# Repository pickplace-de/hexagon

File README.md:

# HEXAGON
HEXAGON is an open hardwrae development board built around 480 MHz Renesas MCU (Arm® Cortex®-M85 core with HeliumTM).<br/>
The board was designed as there was nothing similar meeting our demands at the moment.<br/>
Along with Cortex®-M85 in BGA package the hardware design also includes:<br/>
✔ 8 MB SDRAM<br/>
✔ 32 MB QSPI<br/>
✔ Stereo Audio Codec (for voice recognition applications development) with 3.5mm jack connector for headphones and microphone<br/>
✔ USB interface with USB-C connector (MCU USB and/or power)<br/>
✔ Ethernet interface with RJ45<br/>
✔ CAN interface with D-SUB connector<br/>
✔ RS485 interface with D-SUB connector<br/>
✔ Flexible power supply (from 5 to 30VDC) with barrel jack connector and an option to power the board from USB<br/>
✔ Reset button and power supply LEDs<br/>
✔ 2 user buttons and 3 user LEDs<br/>

## Hardware
The board design contains 8 layers including 4 signal layers, 3 ground planes and 1 power plane.<br/>
Some components (MCU, QSPI) are in BGA packages and may be hard to assembly manually.<br/>

## License
This project is licensed under **CERN-OHL-W-2.0**, which allows modification and commercial use with attribution.<br/>
See the  for full details.

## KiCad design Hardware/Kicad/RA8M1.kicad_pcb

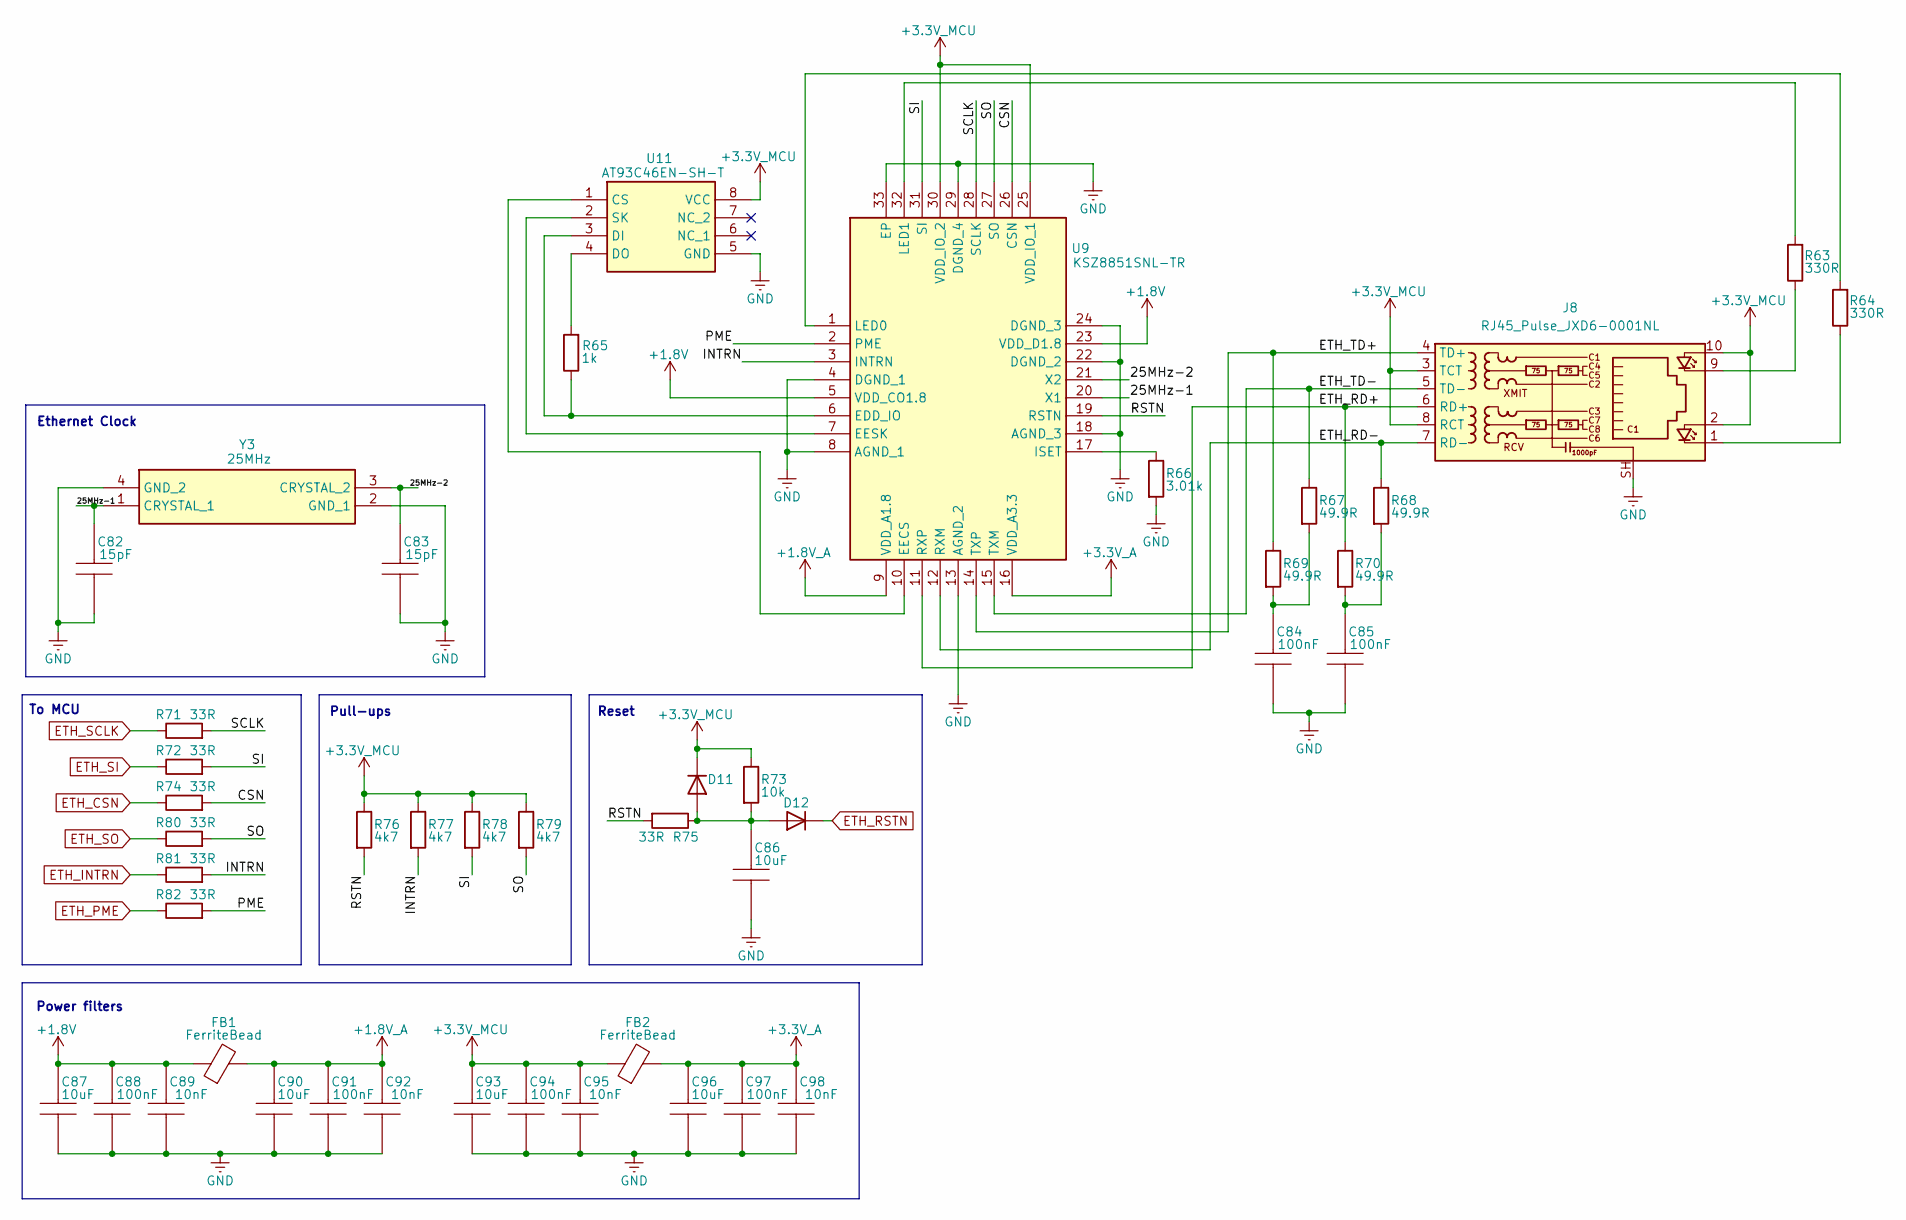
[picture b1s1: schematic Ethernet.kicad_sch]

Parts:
C82, C83: 15pF; C_0402_1005Metric; MPN 885012005008
C84, C85, C88, C91, C94, C97: 100nF; C_0402_1005Metric; MPN 885012205092
C86, C87, C90, C93, C96: 10uF; C_0402_1005Metric; MPN 885012105020
C89, C92, C95, C98: 10nF; C_0402_1005Metric; MPN 885012205031
D11, D12: 1N4148W; D_SOD-123; MPN 1N4148W-7-F
FB1, FB2: FerriteBead; L_0805_2012Metric; MPN 742792040
J8: RJ45_Pulse_JXD6-0001NL; RJ45_Pulse_JXD6-0001NL_Horizontal; MPN JXD6-0001NL
R63, R64: 330R; R_0402_1005Metric; MPN 560112110231
R65: 1k; R_0402_1005Metric; MPN 560112110012
R66: 3.01k; R_0402_1005Metric; MPN CR0402-FX-3011GLF
R67, R68, R69, R70: 49.9R; R_0402_1005Metric; MPN 560112110002
R71, R72, R74, R75, R80, R81, R82: 33R; R_0402_1005Metric; MPN 560112110004
R73: 10k; R_0402_1005Metric; MPN 560112110020
R76, R77, R78, R79: 4k7; R_0402_1005Metric; MPN 560112110245
U9: KSZ8851SNL-TR; QFN50P500X500X100-33N-D; Mouser Part Number 998-KSZ8851SNLTR
U11: AT93C46EN-SH-T; SOIC127P600X175-8N; Mouser Part Number 556-A93C46ENSHT
Y3: 25MHz; 830108208209; Mouser Part Number 830107871909

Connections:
+1.8V: C87.2, C88.2, C89.2, FB1.1, U9.5 (VDD_CO1.8), U9.23 (VDD_D1.8); also elsewhere on the board
+1.8V_A: C90.2, C91.2, C92.2, FB1.2, U9.9 (VDD_A1.8)
+3.3V_A: C96.2, C97.2, C98.2, FB2.2, U9.16 (VDD_A3.3)
+3.3V_MCU: C93.2, C94.2, C95.2, D11.1 (K), FB2.1, J8.2, J8.3 (TCT), J8.8 (RCT), J8.10, R73.1, R76.1, R77.1, R78.1, R79.1, U9.25 (VDD_IO_1), U9.30 (VDD_IO_2), U11.8 (VCC); also elsewhere on the board
/ETHERNET/25MHz-1: C82.2, U9.20 (X1), Y3.1 (CRYSTAL_1)
/ETHERNET/25MHz-2: C83.2, U9.21 (X2), Y3.3 (CRYSTAL_2)
/ETHERNET/CSN: R74.2, U9.26 (CSN)
/ETHERNET/ETH_RD+: J8.6 (RD+), R70.1, U9.11 (RXP)
/ETHERNET/ETH_RD-: J8.7 (RD-), R68.1, U9.12 (RXM)
/ETHERNET/ETH_TD+: J8.4 (TD+), R69.1, U9.14 (TXP)
/ETHERNET/ETH_TD-: J8.5 (TD-), R67.1, U9.15 (TXM)
/ETHERNET/INTRN: R77.2, R81.2, U9.3 (INTRN)
/ETHERNET/PME: R82.2, U9.2 (PME)
/ETHERNET/RSTN: R75.2, R76.2, U9.19 (RSTN)
/ETHERNET/SCLK: R71.2, U9.28 (SCLK)
/ETHERNET/SI: R72.2, R78.2, U9.31 (SI)
/ETHERNET/SO: R79.2, R80.2, U9.27 (SO)
ETH_CSN: R74.1; also elsewhere on the board
ETH_INTRN: R81.1; also elsewhere on the board
ETH_PME: R82.1; also elsewhere on the board
ETH_RSTN: D12.1 (K); also elsewhere on the board
ETH_SCLK: R71.1; also elsewhere on the board
ETH_SI: R72.1; also elsewhere on the board
ETH_SO: R80.1; also elsewhere on the board
GND: C82.1, C83.1, C84.1, C85.1, C86.1, C87.1, C88.1, C89.1, C90.1, C91.1, C92.1, C93.1, C94.1, C95.1, C96.1, C97.1, C98.1, J8.SH, R66.2, U9.4 (DGND_1), U9.8 (AGND_1), U9.13 (AGND_2), U9.18 (AGND_3), U9.22 (DGND_2), U9.24 (DGND_3), U9.29 (DGND_4), U9.33 (EP), U11.5 (GND), Y3.2 (GND_1), Y3.4 (GND_2); also elsewhere on the board
unnamed: C84.2, R67.2, R69.2
unnamed: C85.2, R68.2, R70.2
unnamed: C86.2, D11.2 (A), D12.2 (A), R73.2, R75.1
unnamed: J8.1, R64.1
unnamed: J8.9, R63.1
unnamed: R66.1, U9.17 (ISET)
unnamed: R64.2, U9.1 (LED0)
unnamed: R63.2, U9.32 (LED1)
unnamed: U9.10 (EECS), U11.1 (CS)
unnamed: R65.1, U9.6 (EDD_IO), U11.3 (DI)
unnamed: R65.2, U11.4 (DO)
unnamed: U9.7 (EESK), U11.2 (SK)

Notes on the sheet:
Power filters
To MCU
Pull-ups
Reset
Ethernet Clock

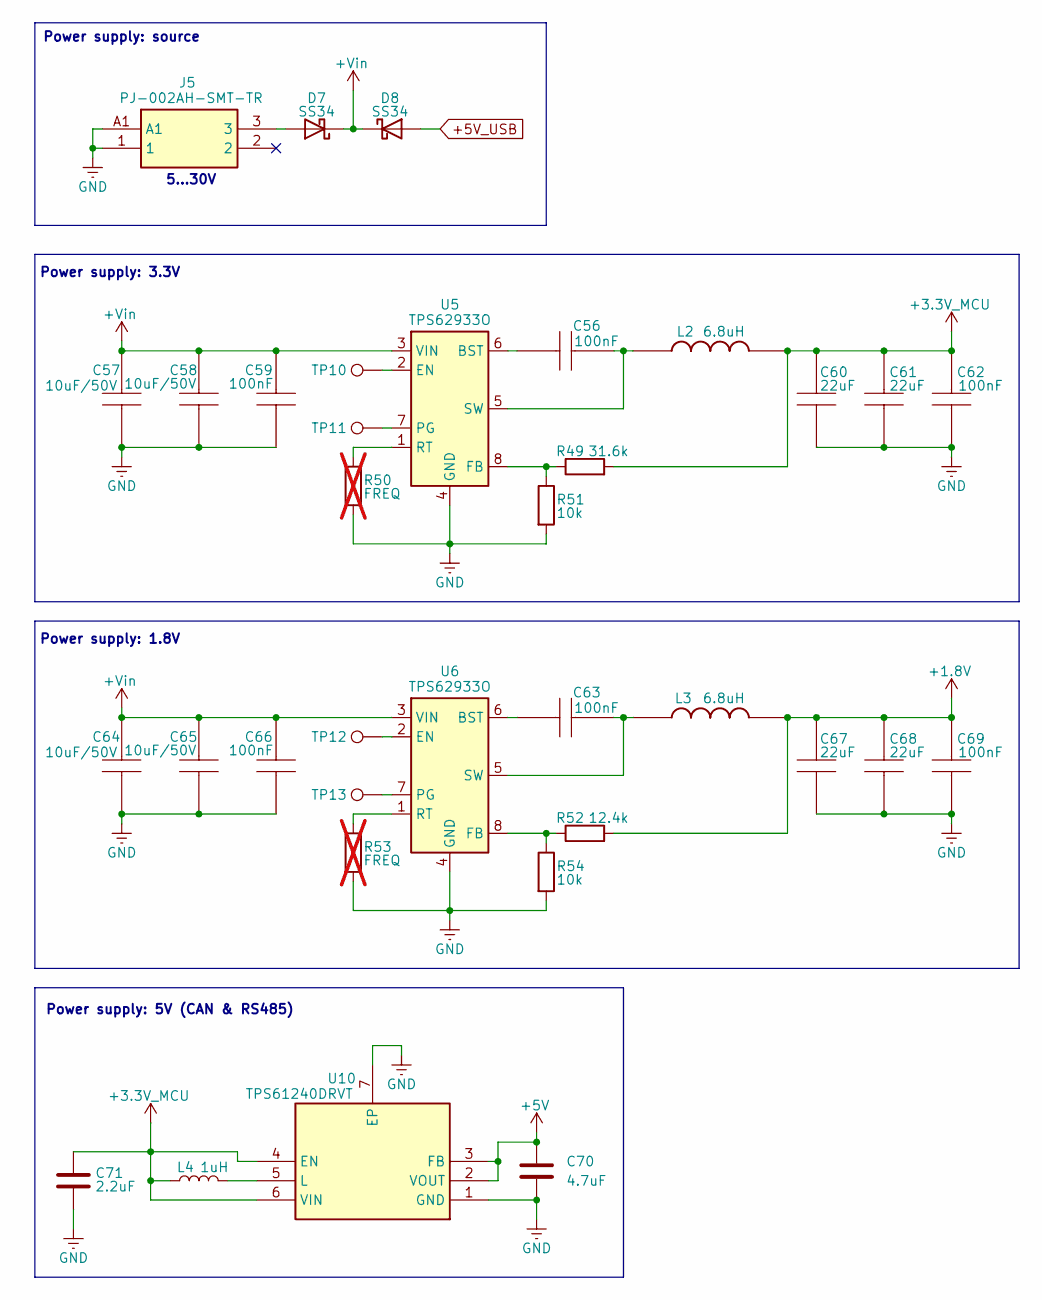
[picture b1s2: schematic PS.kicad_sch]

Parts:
C56, C59, C62, C63, C66, C69: 100nF; C_0402_1005Metric; MPN 885012205092
C57, C58, C64, C65: 10uF/50V; C_0805_2012Metric; MPN C2012X5R1H106K125AC
C60, C61, C67, C68: 22uF; C_0805_2012Metric; MPN 885012107005
C70: 4.7uF; C_0402_1005Metric; MPN 885012105008
C71: 2.2uF; C_0402_1005Metric; MPN 885012105007
D7, D8: SS34; D_SMA
J5: PJ-002AH-SMT-TR; PJ002AHSMTTR; Mouser Part Number 490-PJ-002AH-SMT-TR
L2, L3: 6.8uH; INDPM4141X310N; Mouser Part Number 710-74438357068
L4: 1uH; L_0603_1608Metric; MPN 74479763210A
R49: 31.6k; R_0402_1005Metric; MPN CR0603-FX-3162ELF
R50, R53: FREQ; R_0402_1005Metric; MPN 560112110001; not fitted
R51, R54: 10k; R_0402_1005Metric; MPN 560112110020
R52: 12.4k; R_0402_1005Metric; MPN CR0402-FX-1242GLF
TP10, TP11, TP12, TP13: TestPoint_0.5mm
U5, U6: TPS62933O; SOT-583-8; MPN TPS62933ODRLR
U10: TPS61240DRVT; SON65P200X200X80-7N; Mouser Part Number 595-TPS61240DRVT

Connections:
+1.8V: C67.2, C68.2, C69.2, L3.2, R52.2; also elsewhere on the board
+3.3V_MCU: C60.2, C61.2, C62.2, C71.1, L2.2, L4.1, R49.2, U10.4 (EN), U10.6 (VIN); also elsewhere on the board
+5V: C70.1, U10.2 (VOUT), U10.3 (FB); also elsewhere on the board
+5V_USB: D8.2 (A); also elsewhere on the board
+Vin: C57.2, C58.2, C59.2, C64.2, C65.2, C66.2, D7.1 (K), D8.1 (K), U5.3 (VIN), U6.3 (VIN)
GND: C57.1, C58.1, C59.1, C60.1, C61.1, C62.1, C64.1, C65.1, C66.1, C67.1, C68.1, C69.1, C70.2, C71.2, J5.1, J5.A1, R50.2, R51.2, R53.2, R54.2, U5.4 (GND), U6.4 (GND), U10.1 (GND), U10.7 (EP); also elsewhere on the board
unnamed: D7.2 (A), J5.3
unnamed: C56.2, U5.6 (BST)
unnamed: TP10.1, U5.2 (EN)
unnamed: R49.1, R51.1, U5.8 (FB)
unnamed: TP11.1, U5.7 (PG)
unnamed: R50.1, U5.1 (RT)
unnamed: C56.1, L2.1, U5.5 (SW)
unnamed: C63.2, U6.6 (BST)
unnamed: TP12.1, U6.2 (EN)
unnamed: R52.1, R54.1, U6.8 (FB)
unnamed: TP13.1, U6.7 (PG)
unnamed: R53.1, U6.1 (RT)
unnamed: C63.1, L3.1, U6.5 (SW)
unnamed: L4.2, U10.5 (L)

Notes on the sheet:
Power supply: 5V (CAN & RS485)
Power supply: 3.3V
Power supply: source
Power supply: 1.8V
5...30V

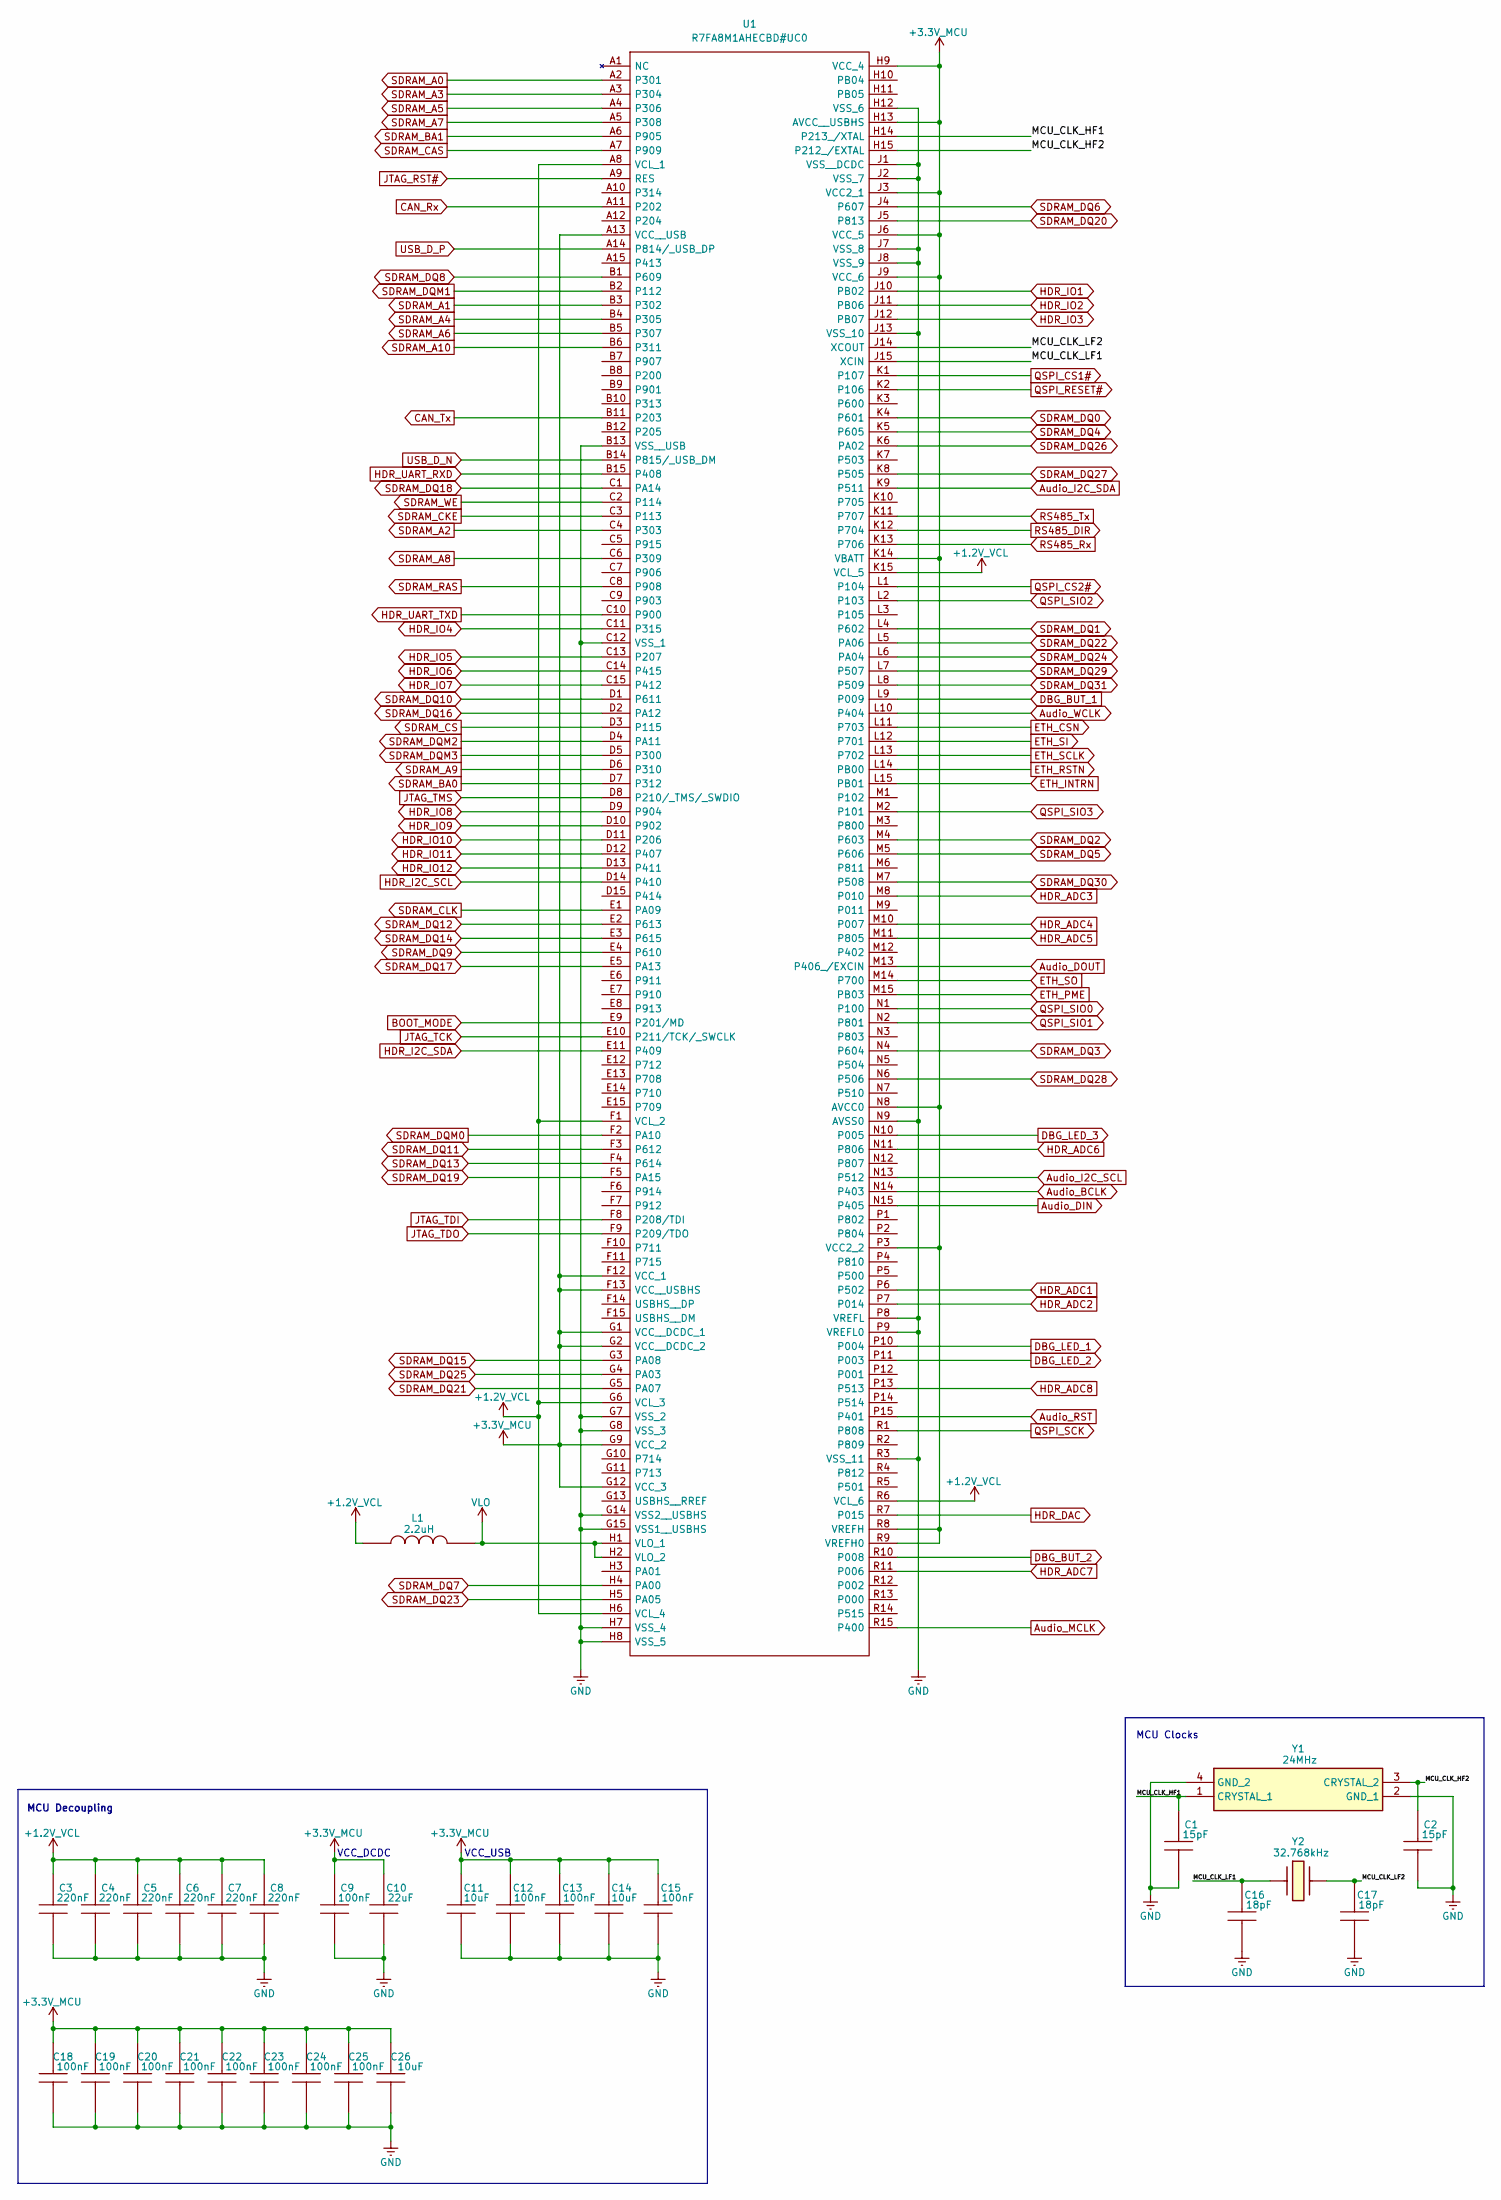
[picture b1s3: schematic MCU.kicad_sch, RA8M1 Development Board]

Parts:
C1, C2: 15pF; C_0402_1005Metric; MPN 885012005008
C3, C4, C5, C6, C7, C8: 220nF; C_0402_1005Metric; MPN 885012105011
C9, C12, C13, C15, C18, C19, C20, C21, C22, C23, C24, C25: 100nF; C_0402_1005Metric; MPN 885012205092
C10: 22uF; C_0805_2012Metric; MPN 885012107005
C11, C14, C26: 10uF; C_0402_1005Metric; MPN 885012105020
C16, C17: 18pF; C_0402_1005Metric; MPN 04023A180CAT2A
L1: 2.2uH; LQM21PHR47NG0D; Mouser Part Number 81-LQM21PN2R2NGCDCD
U1: R7FA8M1AHECBD#UC0; BGA225C80P15X15_1300X1300X147; MPN R7FA8M1AHECBD#UC0
Y1: 24MHz; 830108208209; Mouser Part Number 710-830108208209
Y2: 32.768kHz; 830050789; Mouser Part Number 710-830050789

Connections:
+1.2V_VCL: C3.2, C4.2, C5.2, C6.2, C7.2, C8.2, L1.2, U1.A8 (VCL_1), U1.F1 (VCL_2), U1.G6 (VCL_3), U1.H6 (VCL_4), U1.K15 (VCL_5), U1.R6 (VCL_6)
+3.3V_MCU: C9.2, C10.2, C11.2, C12.2, C13.2, C14.2, C15.2, C18.2, C19.2, C20.2, C21.2, C22.2, C23.2, C24.2, C25.2, C26.2, U1.A13 (VCC__USB), U1.F12 (VCC_1), U1.F13 (VCC__USBHS), U1.G1 (VCC__DCDC_1), U1.G2 (VCC__DCDC_2), U1.G9 (VCC_2), U1.G12 (VCC_3), U1.H9 (VCC_4), U1.H13 (AVCC__USBHS), U1.J3 (VCC2_1), U1.J6 (VCC_5), U1.J9 (VCC_6), U1.K14 (VBATT), U1.N8 (AVCC0), U1.P3 (VCC2_2), U1.R8 (VREFH), U1.R9 (VREFH0); also elsewhere on the board
/MCU/MCU_CLK_HF1: C1.2, U1.H14 (P213_/XTAL), Y1.1 (CRYSTAL_1)
/MCU/MCU_CLK_HF2: C2.2, U1.H15 (P212_/EXTAL), Y1.3 (CRYSTAL_2)
/MCU/MCU_CLK_LF1: C16.2, U1.J15 (XCIN), Y2.1
/MCU/MCU_CLK_LF2: C17.2, U1.J14 (XCOUT), Y2.2
Audio_BCLK: U1.N14 (P403); also elsewhere on the board
Audio_DIN: U1.N15 (P405); also elsewhere on the board
Audio_DOUT: U1.M13 (P406_/EXCIN); also elsewhere on the board
Audio_I2C_SCL: U1.N13 (P512); also elsewhere on the board
Audio_I2C_SDA: U1.K9 (P511); also elsewhere on the board
Audio_MCLK: U1.R15 (P400); also elsewhere on the board
Audio_RST: U1.P15 (P401); also elsewhere on the board
Audio_WCLK: U1.L10 (P404); also elsewhere on the board
BOOT_MODE: U1.E9 (P201/MD); also elsewhere on the board
CAN_Rx: U1.A11 (P202); also elsewhere on the board
CAN_Tx: U1.B11 (P203); also elsewhere on the board
DBG_BUT_1: U1.L9 (P009); also elsewhere on the board
DBG_BUT_2: U1.R10 (P008); also elsewhere on the board
DBG_LED_1: U1.P10 (P004); also elsewhere on the board
DBG_LED_2: U1.P11 (P003); also elsewhere on the board
DBG_LED_3: U1.N10 (P005); also elsewhere on the board
ETH_CSN: U1.L11 (P703); also elsewhere on the board
ETH_INTRN: U1.L15 (PB01); also elsewhere on the board
ETH_PME: U1.M15 (PB03); also elsewhere on the board
ETH_RSTN: U1.L14 (PB00); also elsewhere on the board
ETH_SCLK: U1.L13 (P702); also elsewhere on the board
ETH_SI: U1.L12 (P701); also elsewhere on the board
ETH_SO: U1.M14 (P700); also elsewhere on the board
GND: C1.1, C2.1, C3.1, C4.1, C5.1, C6.1, C7.1, C8.1, C9.1, C10.1, C11.1, C12.1, C13.1, C14.1, C15.1, C16.1, C17.1, C18.1, C19.1, C20.1, C21.1, C22.1, C23.1, C24.1, C25.1, C26.1, U1.B13 (VSS__USB), U1.C12 (VSS_1), U1.G7 (VSS_2), U1.G8 (VSS_3), U1.G14 (VSS2__USBHS), U1.G15 (VSS1__USBHS), U1.H7 (VSS_4), U1.H8 (VSS_5), U1.H12 (VSS_6), U1.J1 (VSS__DCDC), U1.J2 (VSS_7), U1.J7 (VSS_8), U1.J8 (VSS_9), U1.J13 (VSS_10), U1.N9 (AVSS0), U1.P8 (VREFL), U1.P9 (VREFL0), U1.R3 (VSS_11), Y1.2 (GND_1), Y1.4 (GND_2); also elsewhere on the board
HDR_ADC1: U1.P6 (P502); also elsewhere on the board
HDR_ADC2: U1.P7 (P014); also elsewhere on the board
HDR_ADC3: U1.M8 (P010); also elsewhere on the board
HDR_ADC4: U1.M10 (P007); also elsewhere on the board
HDR_ADC5: U1.M11 (P805); also elsewhere on the board
HDR_ADC6: U1.N11 (P806); also elsewhere on the board
HDR_ADC7: U1.R11 (P006); also elsewhere on the board
HDR_ADC8: U1.P13 (P513); also elsewhere on the board
HDR_DAC: U1.R7 (P015); also elsewhere on the board
HDR_I2C_SCL: U1.D14 (P410); also elsewhere on the board
HDR_I2C_SDA: U1.E11 (P409); also elsewhere on the board
HDR_IO1: U1.J10 (PB02); also elsewhere on the board
HDR_IO2: U1.J11 (PB06); also elsewhere on the board
HDR_IO3: U1.J12 (PB07); also elsewhere on the board
HDR_IO4: U1.C11 (P315); also elsewhere on the board
HDR_IO5: U1.C13 (P207); also elsewhere on the board
HDR_IO6: U1.C14 (P415); also elsewhere on the board
HDR_IO7: U1.C15 (P412); also elsewhere on the board
HDR_IO8: U1.D9 (P904); also elsewhere on the board
HDR_IO9: U1.D10 (P902); also elsewhere on the board
HDR_IO10: U1.D11 (P206); also elsewhere on the board
HDR_IO11: U1.D12 (P407); also elsewhere on the board
HDR_IO12: U1.D13 (P411); also elsewhere on the board
HDR_UART_RXD: U1.B15 (P408); also elsewhere on the board
HDR_UART_TXD: U1.C10 (P900); also elsewhere on the board
JTAG_RST#: U1.A9 (RES); also elsewhere on the board
JTAG_TCK: U1.E10 (P211/TCK/_SWCLK); also elsewhere on the board
JTAG_TDI: U1.F8 (P208/TDI); also elsewhere on the board
JTAG_TDO: U1.F9 (P209/TDO); also elsewhere on the board
JTAG_TMS: U1.D8 (P210/_TMS/_SWDIO); also elsewhere on the board
QSPI_CS1#: U1.K1 (P107); also elsewhere on the board
QSPI_CS2#: U1.L1 (P104); also elsewhere on the board
QSPI_RESET#: U1.K2 (P106); also elsewhere on the board
QSPI_SCK: U1.R1 (P808); also elsewhere on the board
QSPI_SIO0: U1.N1 (P100); also elsewhere on the board
QSPI_SIO1: U1.N2 (P801); also elsewhere on the board
QSPI_SIO2: U1.L2 (P103); also elsewhere on the board
QSPI_SIO3: U1.M2 (P101); also elsewhere on the board
RS485_DIR: U1.K12 (P704); also elsewhere on the board
RS485_Rx: U1.K13 (P706); also elsewhere on the board
RS485_Tx: U1.K11 (P707); also elsewhere on the board
SDRAM_A0: U1.A2 (P301); also elsewhere on the board
SDRAM_A1: U1.B3 (P302); also elsewhere on the board
SDRAM_A2: U1.C4 (P303); also elsewhere on the board
SDRAM_A3: U1.A3 (P304); also elsewhere on the board
SDRAM_A4: U1.B4 (P305); also elsewhere on the board
SDRAM_A5: U1.A4 (P306); also elsewhere on the board
SDRAM_A6: U1.B5 (P307); also elsewhere on the board
SDRAM_A7: U1.A5 (P308); also elsewhere on the board
SDRAM_A8: U1.C6 (P309); also elsewhere on the board
SDRAM_A9: U1.D6 (P310); also elsewhere on the board
SDRAM_A10: U1.B6 (P311); also elsewhere on the board
SDRAM_BA0: U1.D7 (P312); also elsewhere on the board
SDRAM_BA1: U1.A6 (P905); also elsewhere on the board
SDRAM_CAS: U1.A7 (P909); also elsewhere on the board
SDRAM_CKE: U1.C3 (P113); also elsewhere on the board
SDRAM_CLK: U1.E1 (PA09); also elsewhere on the board
SDRAM_CS: U1.D3 (P115); also elsewhere on the board
SDRAM_DQ0: U1.K4 (P601); also elsewhere on the board
SDRAM_DQ1: U1.L4 (P602); also elsewhere on the board
SDRAM_DQ2: U1.M4 (P603); also elsewhere on the board
SDRAM_DQ3: U1.N4 (P604); also elsewhere on the board
SDRAM_DQ4: U1.K5 (P605); also elsewhere on the board
SDRAM_DQ5: U1.M5 (P606); also elsewhere on the board
SDRAM_DQ6: U1.J4 (P607); also elsewhere on the board
SDRAM_DQ7: U1.H4 (PA00); also elsewhere on the board
SDRAM_DQ8: U1.B1 (P609); also elsewhere on the board
SDRAM_DQ9: U1.E4 (P610); also elsewhere on the board
SDRAM_DQ10: U1.D1 (P611); also elsewhere on the board
SDRAM_DQ11: U1.F3 (P612); also elsewhere on the board
SDRAM_DQ12: U1.E2 (P613); also elsewhere on the board
SDRAM_DQ13: U1.F4 (P614); also elsewhere on the board
SDRAM_DQ14: U1.E3 (P615); also elsewhere on the board
SDRAM_DQ15: U1.G3 (PA08); also elsewhere on the board
SDRAM_DQ16: U1.D2 (PA12); also elsewhere on the board
SDRAM_DQ17: U1.E5 (PA13); also elsewhere on the board
SDRAM_DQ18: U1.C1 (PA14); also elsewhere on the board
SDRAM_DQ19: U1.F5 (PA15); also elsewhere on the board
SDRAM_DQ20: U1.J5 (P813); also elsewhere on the board
SDRAM_DQ21: U1.G5 (PA07); also elsewhere on the board
SDRAM_DQ22: U1.L5 (PA06); also elsewhere on the board
SDRAM_DQ23: U1.H5 (PA05); also elsewhere on the board
SDRAM_DQ24: U1.L6 (PA04); also elsewhere on the board
SDRAM_DQ25: U1.G4 (PA03); also elsewhere on the board
SDRAM_DQ26: U1.K6 (PA02); also elsewhere on the board
SDRAM_DQ27: U1.K8 (P505); also elsewhere on the board
SDRAM_DQ28: U1.N6 (P506); also elsewhere on the board
SDRAM_DQ29: U1.L7 (P507); also elsewhere on the board
SDRAM_DQ30: U1.M7 (P508); also elsewhere on the board
SDRAM_DQ31: U1.L8 (P509); also elsewhere on the board
SDRAM_DQM0: U1.F2 (PA10); also elsewhere on the board
SDRAM_DQM1: U1.B2 (P112); also elsewhere on the board
SDRAM_DQM2: U1.D4 (PA11); also elsewhere on the board
SDRAM_DQM3: U1.D5 (P300); also elsewhere on the board
SDRAM_RAS: U1.C8 (P908); also elsewhere on the board
SDRAM_WE: U1.C2 (P114); also elsewhere on the board
USB_D_N: U1.B14 (P815/_USB_DM); also elsewhere on the board
USB_D_P: U1.A14 (P814/_USB_DP); also elsewhere on the board
VLO: L1.1, U1.H1 (VLO_1), U1.H2 (VLO_2)

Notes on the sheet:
VCC_USB
MCU Decoupling
VCC_DCDC
MCU Clocks

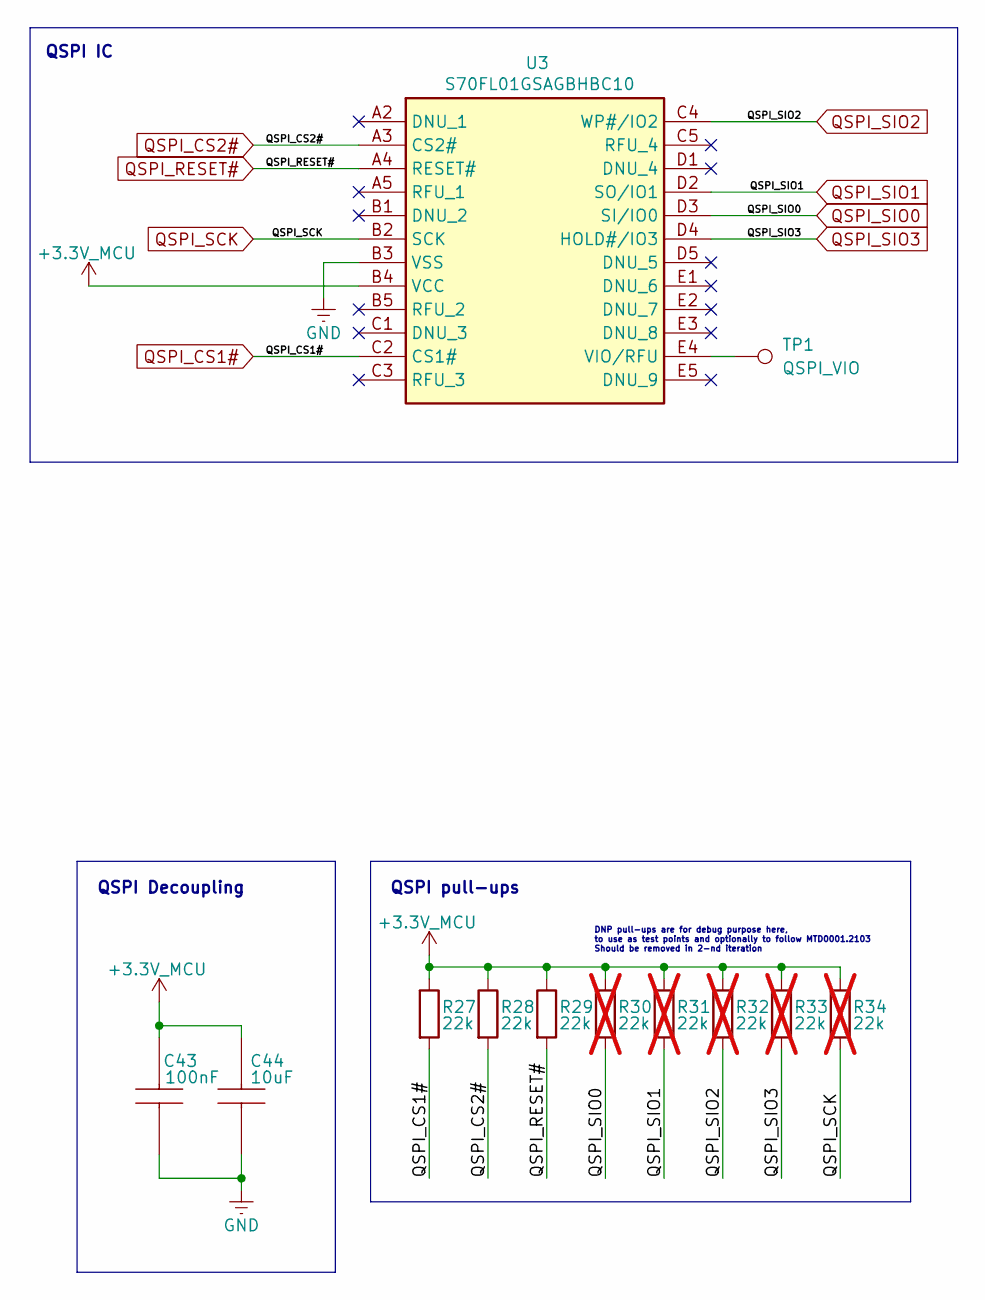
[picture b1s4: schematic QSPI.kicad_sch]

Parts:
C43: 100nF; C_0402_1005Metric; MPN 885012205092
C44: 10uF; C_0402_1005Metric; MPN 885012105020
R27, R28, R29: 22k; R_0402_1005Metric; MPN 560112110098
R30, R31, R32, R33, R34: 22k; R_0402_1005Metric; MPN 560112110098; not fitted
TP1: QSPI_VIO; TestPoint_0.5mm
U3: S70FL01GSAGBHBC10; BGA24C100P5X5_600X800X120; Mouser Part Number 727-S70FL01GSAGBHC10

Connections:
+3.3V_MCU: C43.2, C44.2, R27.1, R28.1, R29.1, R30.1, R31.1, R32.1, R33.1, R34.1, U3.B4 (VCC); also elsewhere on the board
GND: C43.1, C44.1, U3.B3 (VSS); also elsewhere on the board
unnamed: TP1.1, U3.E4 (VIO/RFU)
QSPI_CS1#: R27.2, U3.C2 (CS1#); also elsewhere on the board
QSPI_CS2#: R28.2, U3.A3 (CS2#); also elsewhere on the board
QSPI_RESET#: R29.2, U3.A4 (RESET#); also elsewhere on the board
QSPI_SCK: R34.2, U3.B2 (SCK); also elsewhere on the board
QSPI_SIO0: R30.2, U3.D3 (SI/IO0); also elsewhere on the board
QSPI_SIO1: R31.2, U3.D2 (SO/IO1); also elsewhere on the board
QSPI_SIO2: R32.2, U3.C4 (WP#/IO2); also elsewhere on the board
QSPI_SIO3: R33.2, U3.D4 (HOLD#/IO3); also elsewhere on the board

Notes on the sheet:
QSPI IC
DNP pull-ups are for debug purpose here, to use as test points and optionally to follow MTD0001.2103 Should be removed in 2-nd iteration
QSPI Decoupling
QSPI pull-ups

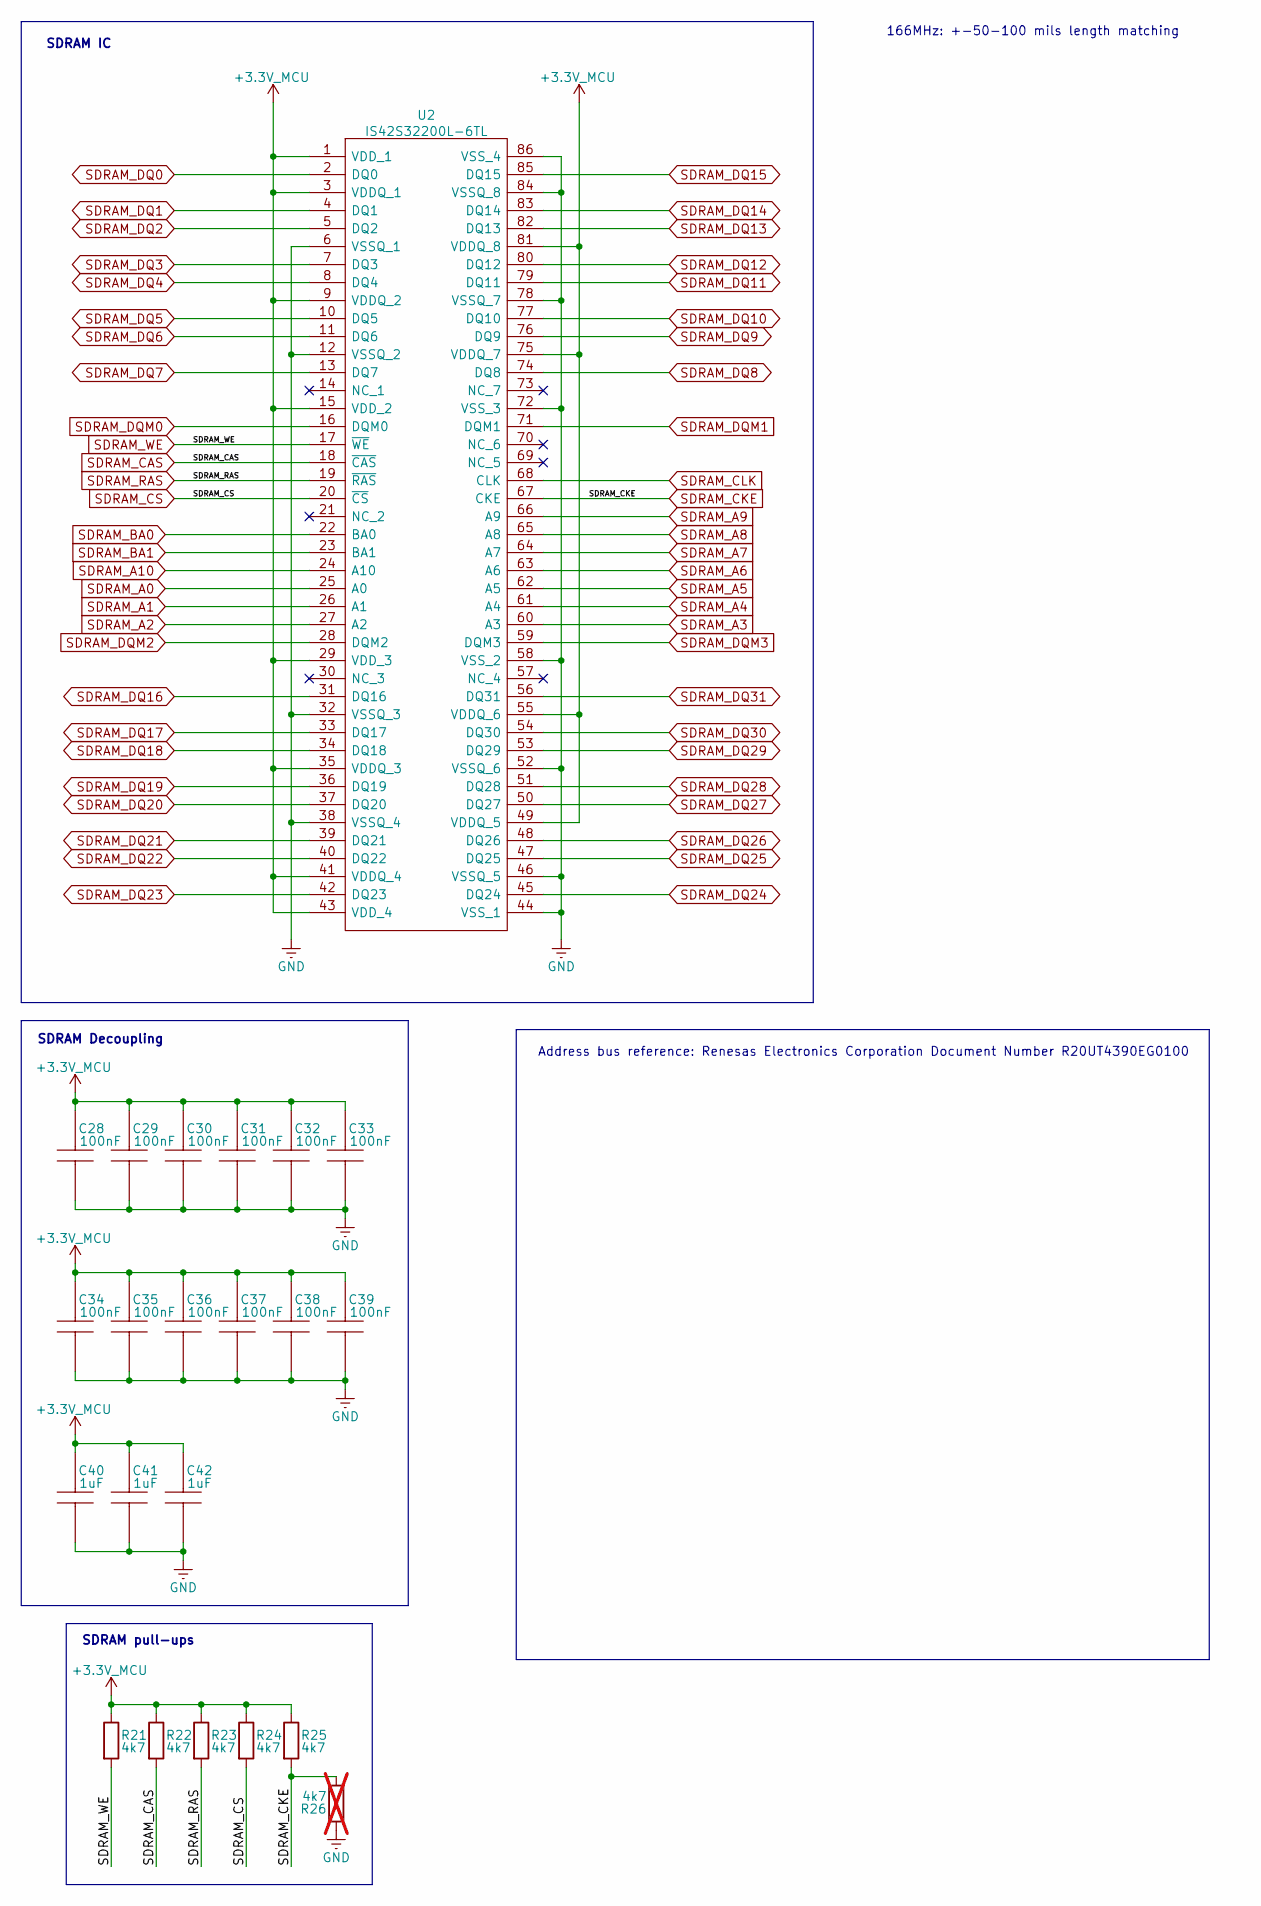
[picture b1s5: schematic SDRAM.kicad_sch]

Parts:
C28, C29, C30, C31, C32, C33, C34, C35, C36, C37, C38, C39: 100nF; C_0402_1005Metric; MPN 885012205092
C40, C41, C42: 1uF; C_0402_1005Metric; MPN 885012105006
R21, R22, R23, R24, R25: 4k7; R_0402_1005Metric; MPN 560112110245
R26: 4k7; R_0402_1005Metric; MPN 560112110245; not fitted
U2: IS42S32200L-6TL; SOP50P1176X120-86N; MPN IS42S32200L-6TL

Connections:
+3.3V_MCU: C28.2, C29.2, C30.2, C31.2, C32.2, C33.2, C34.2, C35.2, C36.2, C37.2, C38.2, C39.2, C40.2, C41.2, C42.2, R21.1, R22.1, R23.1, R24.1, R25.1, U2.1 (VDD_1), U2.3 (VDDQ_1), U2.9 (VDDQ_2), U2.15 (VDD_2), U2.29 (VDD_3), U2.35 (VDDQ_3), U2.41 (VDDQ_4), U2.43 (VDD_4), U2.49 (VDDQ_5), U2.55 (VDDQ_6), U2.75 (VDDQ_7), U2.81 (VDDQ_8); also elsewhere on the board
GND: C28.1, C29.1, C30.1, C31.1, C32.1, C33.1, C34.1, C35.1, C36.1, C37.1, C38.1, C39.1, C40.1, C41.1, C42.1, R26.1, U2.6 (VSSQ_1), U2.12 (VSSQ_2), U2.32 (VSSQ_3), U2.38 (VSSQ_4), U2.44 (VSS_1), U2.46 (VSSQ_5), U2.52 (VSSQ_6), U2.58 (VSS_2), U2.72 (VSS_3), U2.78 (VSSQ_7), U2.84 (VSSQ_8), U2.86 (VSS_4); also elsewhere on the board
SDRAM_A0: U2.25 (A0); also elsewhere on the board
SDRAM_A1: U2.26 (A1); also elsewhere on the board
SDRAM_A2: U2.27 (A2); also elsewhere on the board
SDRAM_A3: U2.60 (A3); also elsewhere on the board
SDRAM_A4: U2.61 (A4); also elsewhere on the board
SDRAM_A5: U2.62 (A5); also elsewhere on the board
SDRAM_A6: U2.63 (A6); also elsewhere on the board
SDRAM_A7: U2.64 (A7); also elsewhere on the board
SDRAM_A8: U2.65 (A8); also elsewhere on the board
SDRAM_A9: U2.66 (A9); also elsewhere on the board
SDRAM_A10: U2.24 (A10); also elsewhere on the board
SDRAM_BA0: U2.22 (BA0); also elsewhere on the board
SDRAM_BA1: U2.23 (BA1); also elsewhere on the board
SDRAM_CAS: R22.2, U2.18 (~CAS); also elsewhere on the board
SDRAM_CKE: R25.2, R26.2, U2.67 (CKE); also elsewhere on the board
SDRAM_CLK: U2.68 (CLK); also elsewhere on the board
SDRAM_CS: R24.2, U2.20 (~CS); also elsewhere on the board
SDRAM_DQ0: U2.2 (DQ0); also elsewhere on the board
SDRAM_DQ1: U2.4 (DQ1); also elsewhere on the board
SDRAM_DQ2: U2.5 (DQ2); also elsewhere on the board
SDRAM_DQ3: U2.7 (DQ3); also elsewhere on the board
SDRAM_DQ4: U2.8 (DQ4); also elsewhere on the board
SDRAM_DQ5: U2.10 (DQ5); also elsewhere on the board
SDRAM_DQ6: U2.11 (DQ6); also elsewhere on the board
SDRAM_DQ7: U2.13 (DQ7); also elsewhere on the board
SDRAM_DQ8: U2.74 (DQ8); also elsewhere on the board
SDRAM_DQ9: U2.76 (DQ9); also elsewhere on the board
SDRAM_DQ10: U2.77 (DQ10); also elsewhere on the board
SDRAM_DQ11: U2.79 (DQ11); also elsewhere on the board
SDRAM_DQ12: U2.80 (DQ12); also elsewhere on the board
SDRAM_DQ13: U2.82 (DQ13); also elsewhere on the board
SDRAM_DQ14: U2.83 (DQ14); also elsewhere on the board
SDRAM_DQ15: U2.85 (DQ15); also elsewhere on the board
SDRAM_DQ16: U2.31 (DQ16); also elsewhere on the board
SDRAM_DQ17: U2.33 (DQ17); also elsewhere on the board
SDRAM_DQ18: U2.34 (DQ18); also elsewhere on the board
SDRAM_DQ19: U2.36 (DQ19); also elsewhere on the board
SDRAM_DQ20: U2.37 (DQ20); also elsewhere on the board
SDRAM_DQ21: U2.39 (DQ21); also elsewhere on the board
SDRAM_DQ22: U2.40 (DQ22); also elsewhere on the board
SDRAM_DQ23: U2.42 (DQ23); also elsewhere on the board
SDRAM_DQ24: U2.45 (DQ24); also elsewhere on the board
SDRAM_DQ25: U2.47 (DQ25); also elsewhere on the board
SDRAM_DQ26: U2.48 (DQ26); also elsewhere on the board
SDRAM_DQ27: U2.50 (DQ27); also elsewhere on the board
SDRAM_DQ28: U2.51 (DQ28); also elsewhere on the board
SDRAM_DQ29: U2.53 (DQ29); also elsewhere on the board
SDRAM_DQ30: U2.54 (DQ30); also elsewhere on the board
SDRAM_DQ31: U2.56 (DQ31); also elsewhere on the board
SDRAM_DQM0: U2.16 (DQM0); also elsewhere on the board
SDRAM_DQM1: U2.71 (DQM1); also elsewhere on the board
SDRAM_DQM2: U2.28 (DQM2); also elsewhere on the board
SDRAM_DQM3: U2.59 (DQM3); also elsewhere on the board
SDRAM_RAS: R23.2, U2.19 (~RAS); also elsewhere on the board
SDRAM_WE: R21.2, U2.17 (~WE); also elsewhere on the board

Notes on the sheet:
SDRAM pull-ups
SDRAM Decoupling
SDRAM IC
Address bus reference: Renesas Electronics Corporation Document Number R20UT4390EG0100
166MHz: +-50-100 mils length matching
